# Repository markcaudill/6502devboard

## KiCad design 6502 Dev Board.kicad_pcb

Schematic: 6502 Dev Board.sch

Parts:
C1: .22uF; C_Disc_D5.0mm_W2.5mm_P2.50mm
C2, C3: .1uF; C_Disc_D5.0mm_W2.5mm_P2.50mm
C4: 10uF; CP_Radial_D5.0mm_P2.50mm
C5, C6, C7, C8: 1uF; C_Disc_D5.0mm_W2.5mm_P2.50mm
D1, D2, D3, D4: D; D_DO-41_SOD81_P7.62mm_Horizontal
J1: Barrel_Jack; BarrelJack_Horizontal
J2: Signals; PinHeader_2x12_P2.54mm_Vertical
J3: Addresses; PinHeader_1x16_P2.54mm_Vertical
J4: Data; PinHeader_1x08_P2.54mm_Vertical
JP1: Jumper; PinHeader_1x02_P2.54mm_Vertical
R1, R2, R3, R4, R5, R6, R7, R8, R9, R10: 10k; R_Axial_DIN0207_L6.3mm_D2.5mm_P7.62mm_Horizontal
SW1: Power; SW_DIP_SPDTx01_Slide_13x7mm_W710mm_P5mm_LowProfile
SW2: Reset; SW_PUSH_6mm
U1: W65C02S; DIP-40_W15.24mm_Socket
U2: 62256; DIP-28_W15.24mm_Socket
U3: L7805; TO-220F-3_Horizontal_TabUp
U4: DS1233; TO-92
U5: 28C256; DIP-28_W15.24mm_Socket
U6: GAL22V10; DIP-24_W10.16mm_Socket
X1: 1.8432; Oscillator_DIP-14

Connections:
+5V: C2.1, C4.1, C5.1, C6.1, C7.1, C8.1, J2.23, R1.1, R2.1, R3.1, R4.1, R5.1, R6.1, R7.1, R8.1, R9.1, R10.1, U1.8, U2.28, U3.3 (OUT), U4.3, U5.28 (VCC), U6.24, X1.14 (Vcc)
/A0: J3.1, U1.9, U2.10, U5.10 (A0)
/A1: J3.2, U1.10, U2.9, U5.9 (A1)
/A2: J3.3, U1.11, U2.8, U5.8 (A2)
/A3: J3.4, U1.12, U2.7, U5.7 (A3)
/A4: J3.5, U1.13, U2.6, U5.6 (A4), U6.3
/A5: J3.6, U1.14, U2.5, U5.5 (A5), U6.4
/A6: J3.7, U1.15, U2.4, U5.4 (A6), U6.5
/A7: J3.8, U1.16, U2.3, U5.3 (A7), U6.6
/A8: J3.9, U1.17, U2.25, U5.25 (A8), U6.7
/A9: J3.10, U1.18, U2.24, U5.24 (A9), U6.8
/A10: J3.11, U1.19, U2.21, U5.21 (A10), U6.9
/A11: J3.12, U1.20, U2.23, U5.23 (A11), U6.10
/A12: J3.13, U1.22, U2.2, U5.2 (A12), U6.11
/A13: J3.14, U1.23, U2.26, U5.26 (A13), U6.13
/A14: J3.15, U1.24, U2.1, U5.1 (A14), U6.14
/A15: J3.16, U1.25, U6.15
/BE: J2.10, R6.2, U1.36
/D0: J4.1, U1.33, U2.11, U5.11 (D0)
/D1: J4.2, U1.32, U2.12, U5.12 (D1)
/D2: J4.3, U1.31, U2.13, U5.13 (D2)
/D3: J4.4, U1.30, U2.15, U5.15 (D3)
/D4: J4.5, U1.29, U2.16, U5.16 (D4)
/D5: J4.6, U1.28, U2.17, U5.17 (D5)
/D6: J4.7, U1.27, U2.18, U5.18 (D6)
/D7: J4.8, U1.26, U2.19, U5.19 (D7)
/PHI1O: J2.5, U1.3
/PHI2: J2.8, JP1.2, U1.37, U6.1
/PHI2O: J2.4, U1.39
/RDY: J2.3, R3.2, U1.2
/R~W: J2.13, U1.34, U6.2
/SYNC: J2.12, U1.7
/~IO1: J2.17, U6.20
/~IO2: J2.16, U6.21
/~IO3: J2.15, U6.22
/~IO4: J2.14, U6.23
/~IRQ: J2.7, R2.2, U1.4
/~ML: J2.9, U1.5
/~NMI: J2.11, R1.2, U1.6
/~OE: J2.21, R10.2, U2.22, U5.22 (~OE), U6.16
/~RAM: J2.19, R9.2, U2.20, U6.18
/~RES: C3.2, J2.2, R4.2, SW2.1, U1.40, U4.2
/~ROM: J2.18, R7.2, U5.20 (~CS), U6.19
/~SO: J2.6, R5.2, U1.38
/~VP: J2.1, U1.1
/~WE: J2.20, R8.2, U2.27, U5.27 (~WE), U6.17
GND: C1.2, C2.2, C3.1, C4.2, C5.2, C6.2, C7.2, C8.2, D3.2 (A), D4.2 (A), J2.24, SW2.2, U1.21, U2.14, U3.2 (GND), U4.1, U5.14 (GND), U6.12, X1.7 (GND)
unnamed: C1.1, D1.1 (K), D2.1 (K), U3.1 (IN)
unnamed: D1.2 (A), D3.1 (K), SW1.2 (B)
unnamed: D2.2 (A), D4.1 (K), J1.2
unnamed: J1.1, SW1.1 (A)
unnamed: JP1.1, X1.8 (OUT)

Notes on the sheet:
Microprocessor
RAM
ROM
Address Decoder
Clock
Power Monitor & Reset
Power Input & Regulator
Place Pull-up Resistors Near Inputs
Place Decoupling Capacitors Near VCC on ICs Place Polarized Capacitor Near +5V Supply

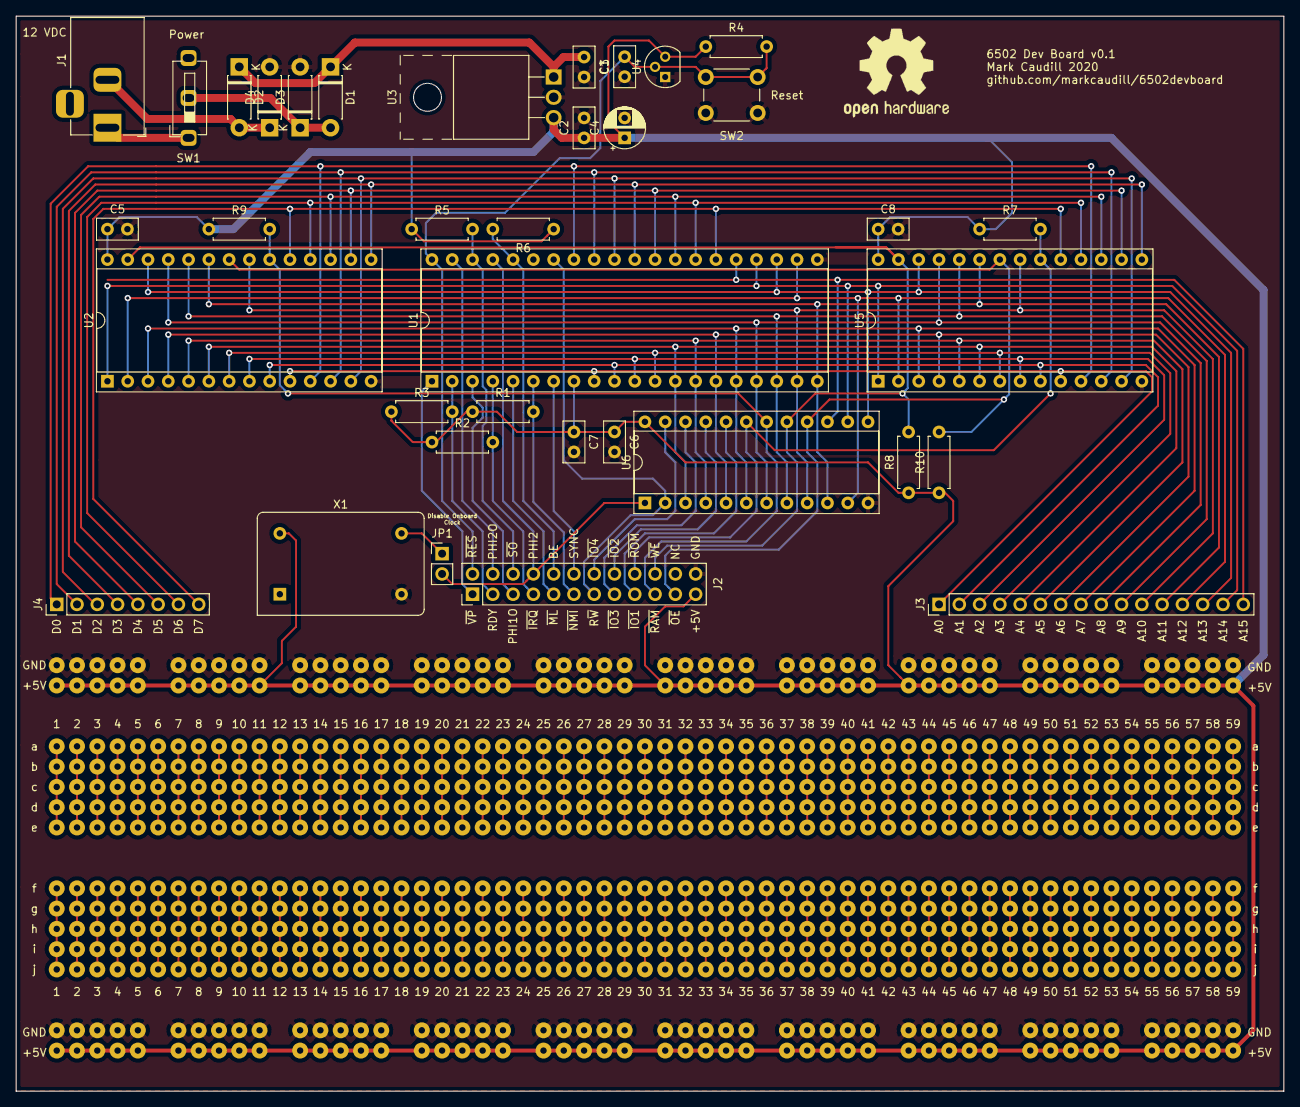
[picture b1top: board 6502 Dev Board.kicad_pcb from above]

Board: 2 copper layers, 158.8 x 134.6 mm, 36 parts (0 on the bottom side), 52 nets.

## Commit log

2020-09-06 Initial commit.
2020-09-06 Add pictures.
2020-09-06 Update metadata.
